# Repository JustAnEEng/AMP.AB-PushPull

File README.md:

# Amplificador de Potencia de Audio Clase AB

Proyecto de diseño, simulación, implementación de circuito impreso (PCB) y caracterización experimental de un amplificador de audio de potencia con topología Clase AB push-pull y su fuente de alimentacion, desarrollado en el marco de la cátedra **Electrónica I** de la **Universidad Nacional del Nordeste (UNNE)**.

## Descripción General y Especificaciones Técnicas

El sistema consiste en un amplificador integrado de dos etapas: una etapa preamplificadora basada en un amplificador operacional **NE5532** (en configuracion no inversora) seguida de una etapa de salida complementaria en configuración **Clase AB push-pull** con red de compensación de estabilidad de Zobel. El sistema de alimentacion del amplificador esta dado por una fuente de punto medio basada en el circuito doblador de tension de onda completa y regulada por diodos zener, se hace uso de transistores de paso.

* **Potencia de salida nominal:** 6,5 W
* **Ganancia de potencia total:** 60 dB
* **Ancho de banda (NOMINAL):** 20 kHz
* **Alimentación:** Fuente partida simétrica (+Vcc = 16V; -Vcc = 16V)
* **Tecnología de montaje:** Componentes de inserción sobre placa de circuito impreso de capa simple.
* **Rendimiento:** 50%

## Estructura del Repositorio

```text
├── KiCad/          # Archivos de proyecto, esquemáticos y diseño de PCB (.kicad_pro, .kicad_sch, .kicad_pcb)
├── Proteus/        # Modelos de simulación circuital y análisis en frecuencia/transitorio (.asc, .pdsprj)
├── Varios/         # Informe técnico, memorias de cálculo y hojas de datos de componentes
└── .gitignore      # Exclusión de archivos temporales y respaldos automáticos de software

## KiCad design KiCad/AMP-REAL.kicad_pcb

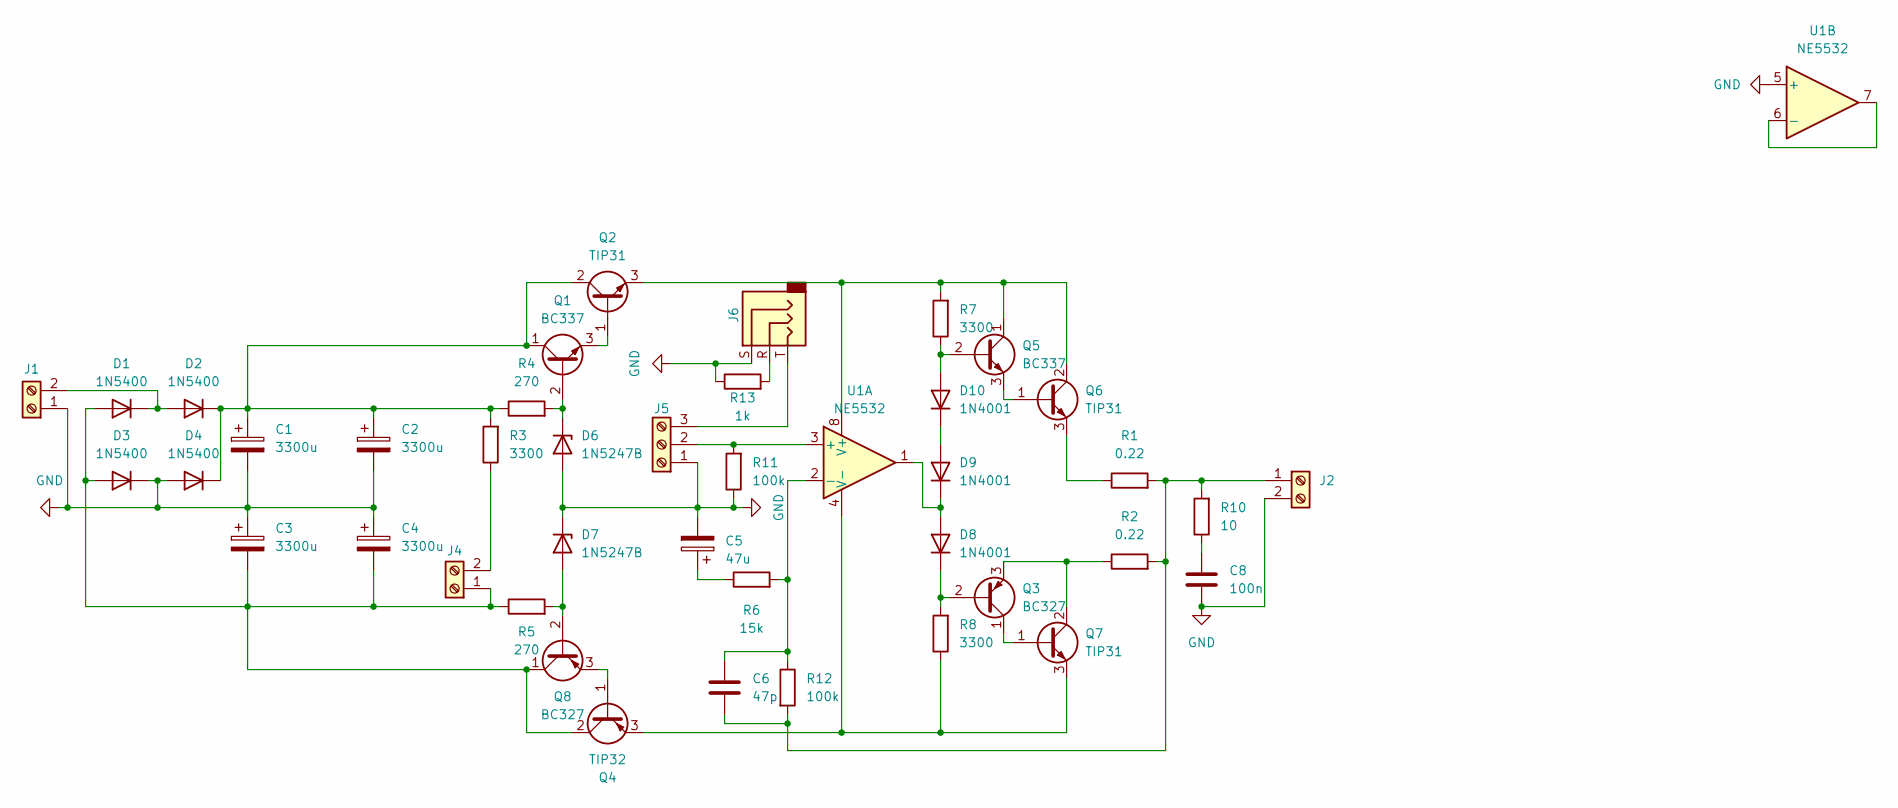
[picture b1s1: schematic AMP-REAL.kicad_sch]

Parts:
C1, C2, C3, C4: 3300u; CP_Radial_D18.0mm_P7.50mm
C5: 47u; CP_Radial_D6.3mm_P2.50mm
C6: 47p; C_Disc_D7.5mm_W2.5mm_P5.00mm
C8: 100n; C_Rect_L7.2mm_W3.5mm_P5.00mm_FKS2_FKP2_MKS2_MKP2
D1, D2, D3, D4: 1N5400; D_DO-201AD_P15.24mm_Horizontal
D6, D7: 1N5247B; D_DO-35_SOD27_P10.16mm_Horizontal
D8, D9, D10: 1N4001; D_DO-41_SOD81_P10.16mm_Horizontal
J1, J2, J4: Screw_Terminal_01x02; TerminalBlock_Phoenix_MKDS-1,5-2_1x02_P5.00mm_Horizontal
J5: Screw_Terminal_01x03; TerminalBlock_Phoenix_MKDS-1,5-3-5.08_1x03_P5.08mm_Horizont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
J6: AudioJack3; Jack_3.5mm_CUI_SJ1-3523N_Horizontal
Q1, Q5: BC337; TO-92
Q2, Q6, Q7: TIP31; TO-220-3_Vertical
Q3, Q8: BC327; TO-92
Q4: TIP32; TO-220-3_Vertical
R1, R2: 0.22; R_Axial_Power_L25.0mm_W9.0mm_P30.48mm
R3, R7, R8: 3300; R_Axial_DIN0411_L9.9mm_D3.6mm_P12.70mm_Horizontal
R4, R5: 270; R_Axial_DIN0414_L11.9mm_D4.5mm_P15.24mm_Horizontal
R6: 15k; R_Axial_DIN0411_L9.9mm_D3.6mm_P12.70mm_Horizontal
R10: 10; R_Axial_DIN0414_L11.9mm_D4.5mm_P15.24mm_Horizontal
R11, R12: 100k; R_Axial_DIN0411_L9.9mm_D3.6mm_P12.70mm_Horizontal
R13: 1k; R_Axial_DIN0411_L9.9mm_D3.6mm_P12.70mm_Horizontal
U1: NE5532; DIP-8_W7.62mm_Socket_LongPads

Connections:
GND: C1.2, C2.2, C3.1, C4.1, C5.2, C8.1, D3.1 (K), D4.2 (A), D6.2 (A), D7.1 (K), J1.1, J2.2, J5.1, J6.S, R11.1, R13.1, U1.5 (+)
unnamed: C5.1, R6.1
unnamed: C8.2, R10.1
unnamed: C3.2, C4.2, D1.2 (A), D3.2 (A), J4.1, Q4.2 (C), Q8.1 (C), R5.1
unnamed: D1.1 (K), D2.2 (A), J1.2
unnamed: C1.1, C2.1, D2.1 (K), D4.1 (K), Q1.1 (C), Q2.2 (C), R3.2, R4.1
unnamed: D6.1 (K), Q1.2 (B), R4.2
unnamed: D7.2 (A), Q8.2 (B), R5.2
unnamed: D8.2 (A), D9.1 (K), U1.1
unnamed: D8.1 (K), Q3.2 (B), R8.2
unnamed: D10.2 (A), Q5.2 (B), R7.1
unnamed: D9.2 (A), D10.1 (K)
unnamed: C6.2, J2.1, R1.2, R2.2, R10.2, R12.2
unnamed: J4.2, R3.1
unnamed: J5.2, R11.2, U1.3 (+)
unnamed: J5.3, J6.T
unnamed: J6.R, R13.2
unnamed: Q1.3 (E), Q2.1 (B)
unnamed: Q2.3 (E), Q5.1 (C), Q6.2 (C), R7.2, U1.8 (V+)
unnamed: Q3.1 (C), Q7.1 (B)
unnamed: Q3.3 (E), Q7.2 (C), R2.1
unnamed: Q4.1 (B), Q8.3 (E)
unnamed: Q4.3 (E), Q7.3 (E), R8.1, U1.4 (V-)
unnamed: Q5.3 (E), Q6.1 (B)
unnamed: Q6.3 (E), R1.1
unnamed: C6.1, R6.2, R12.1, U1.2 (-)
unnamed: U1.6 (-), U1.7

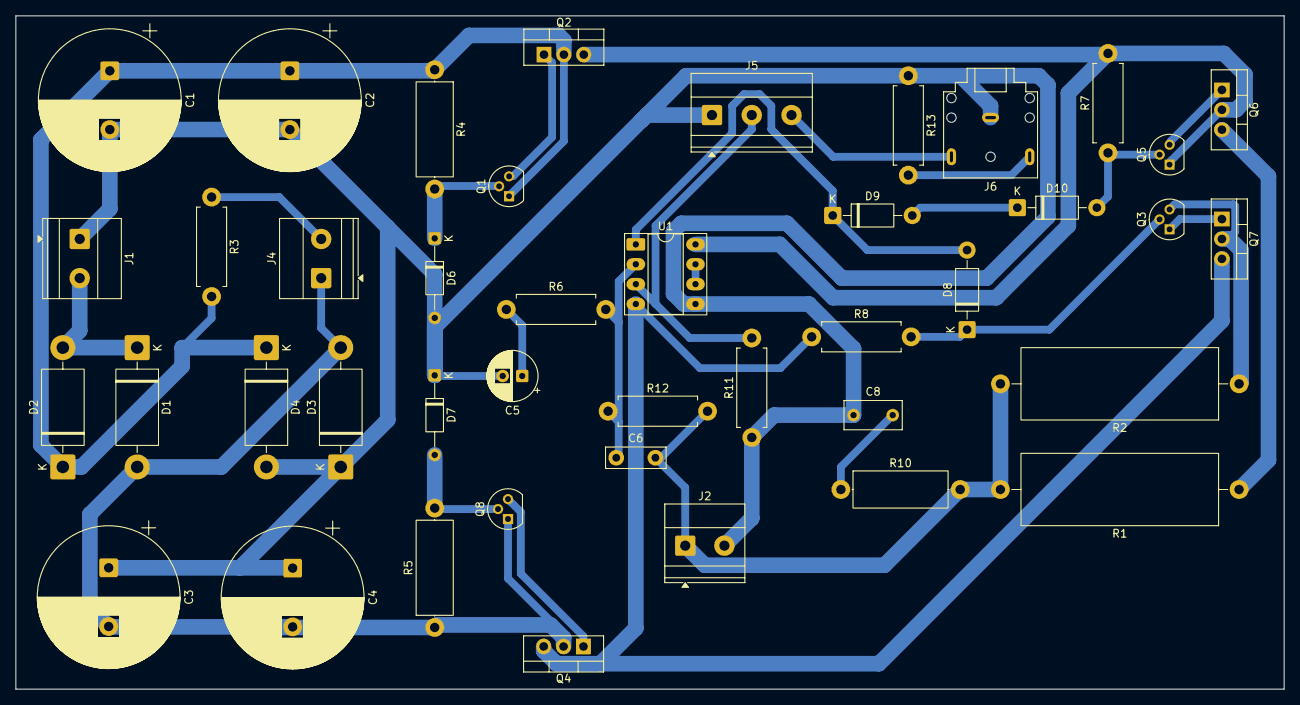
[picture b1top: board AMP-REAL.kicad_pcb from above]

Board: 2 copper layers, 162.0 x 86.0 mm, 42 parts (0 on the bottom side), 27 nets.
